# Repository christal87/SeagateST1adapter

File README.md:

# SeagateST1adapter

This is a quick and dirty 40 or 44 pin IDE adapter for Seagate ST1 drives with ATA Flex interface.  
These drives were common in mid- to high-end portable music players between 2000-2008.  

My PCB was quickly routed with FreeRouting using an exported Specctra session file from KiCAD.  
I have tested raw and unpartitioned writes with dd, filling an ST650211FX disk with about 1GB of zeroes shown 3MB/s throughtput at an average.  
  
Check out the wikipedia article about these disks [here](https://en.wikipedia.org/wiki/Seagate_ST1).  
Also Hans-Jürgen Reggel experimented with them awhile ago. Which you can see [here](http://www.hjreggel.net/hdtechdat/hd-seagate.html).  
  
##### Known ST1 HDDs with ATA Flex interface:
  
- ST625211FX (2.5GB) (2004)
- ST650211FX (5GB) (2004)
- ST64022FX (4GB) (2005)
- ST66022FX (6GB) (2005)
- ST68022FX (8GB) (2005)

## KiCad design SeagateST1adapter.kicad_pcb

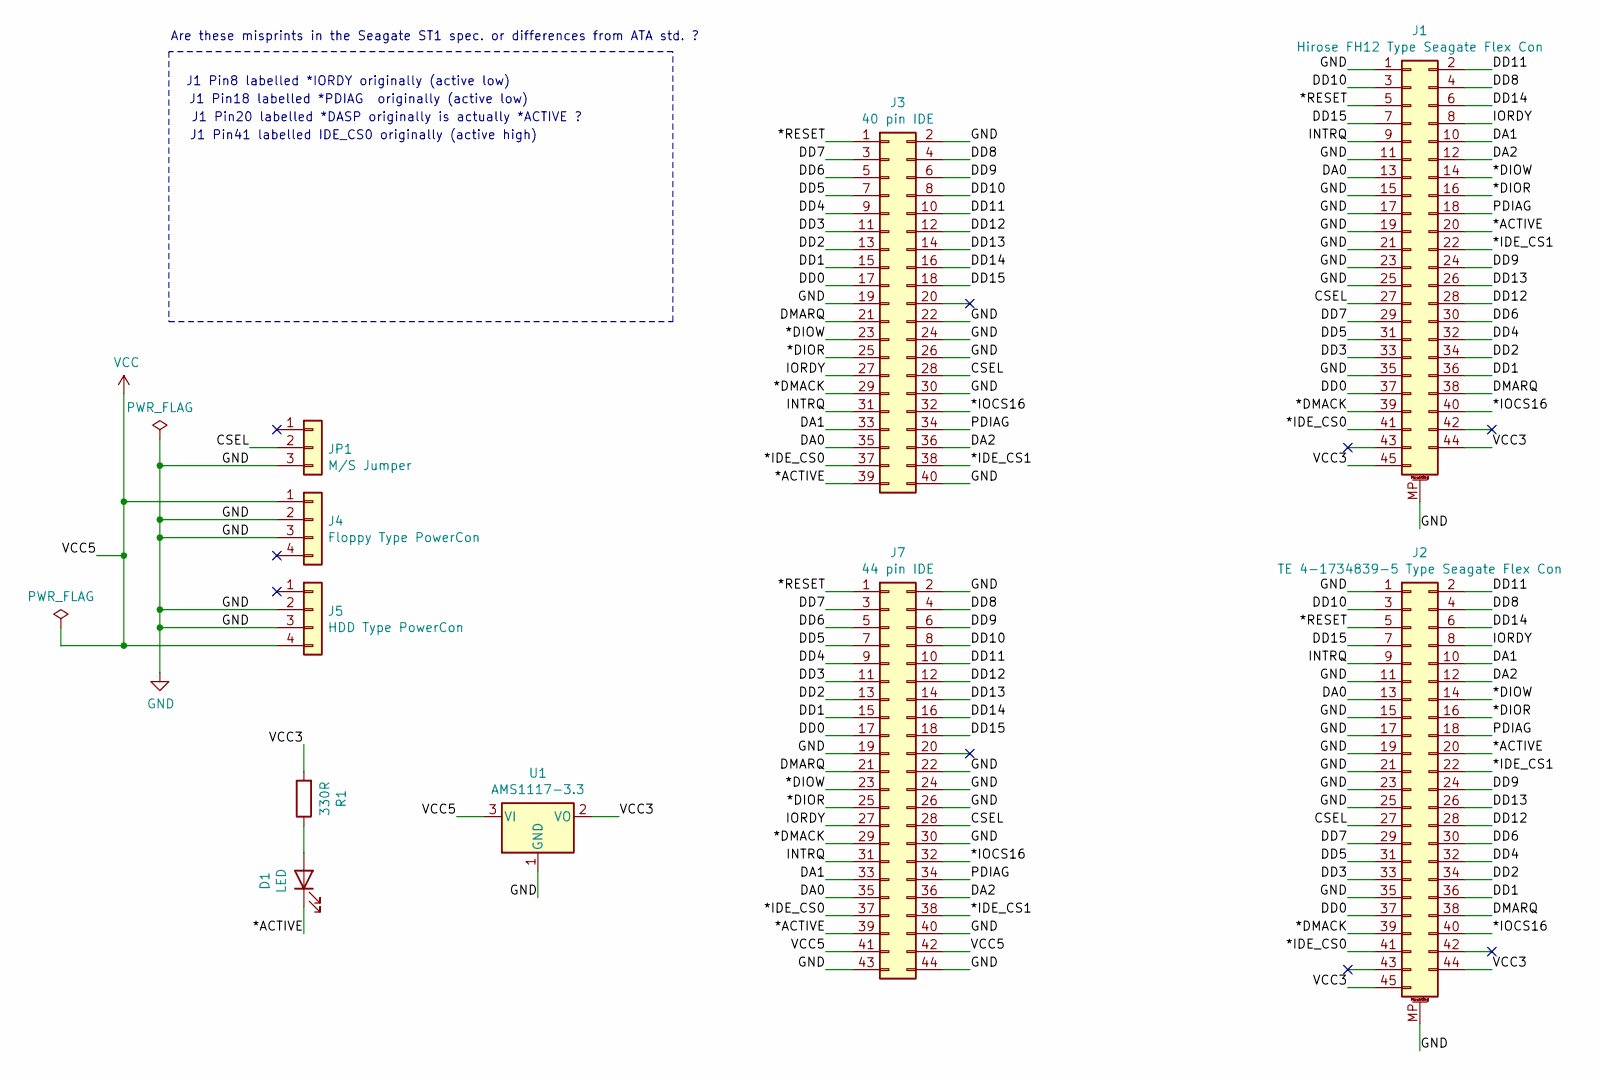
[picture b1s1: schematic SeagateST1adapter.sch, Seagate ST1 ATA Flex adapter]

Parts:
D1: LED; LED_D3.0mm
J1: Hirose FH12 Type Seagate Flex Con; Hirose_FH12-45S-0.5SH_1x45-1MP_P0.50mm_Horizontal
J2: TE 4-1734839-5 Type Seagate Flex Con; TE_4-1734839-5_1x45-1MP_P0.5mm_Horizontal
J3: 40 pin IDE; IDC-Header_2x20_P2.54mm_Vertical
J4: Floppy Type PowerCon; Molex_KK-254_AE-6410-04A_1x04_P2.54mm_Vertical
J5: HDD Type PowerCon; TE_MATE-N-LOK_350211-1_1x04_P5.08mm_Vertical
J7: 44 pin IDE; PinHeader_2x22_P2.00mm_Vertical
JP1: M/S Jumper; PinHeader_1x03_P2.54mm_Vertical
R1: 330R; R_Axial_DIN0207_L6.3mm_D2.5mm_P7.62mm_Horizontal
U1: AMS1117-3.3; SOT-223-3_TabPin2

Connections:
/*ACTIVE: D1.1 (K), J1.20, J2.20, J3.39, J7.39
/*DIOR: J1.16, J2.16, J3.25, J7.25
/*DIOW: J1.14, J2.14, J3.23, J7.23
/*DMACK: J1.39, J2.39, J3.29, J7.29
/*IDE_CS0: J1.41, J2.41, J3.37, J7.37
/*IDE_CS1: J1.22, J2.22, J3.38, J7.38
/*IOCS16: J1.40, J2.40, J3.32, J7.32
/*RESET: J1.5, J2.5, J3.1, J7.1
/CSEL: J1.27, J2.27, J3.28, J7.28, JP1.2
/DA0: J1.13, J2.13, J3.35, J7.35
/DA1: J1.10, J2.10, J3.33, J7.33
/DA2: J1.12, J2.12, J3.36, J7.36
/DD0: J1.37, J2.37, J3.17, J7.17
/DD1: J1.36, J2.36, J3.15, J7.15
/DD2: J1.34, J2.34, J3.13, J7.13
/DD3: J1.33, J2.33, J3.11, J7.11
/DD4: J1.32, J2.32, J3.9, J7.9
/DD5: J1.31, J2.31, J3.7, J7.7
/DD6: J1.30, J2.30, J3.5, J7.5
/DD7: J1.29, J2.29, J3.3, J7.3
/DD8: J1.4, J2.4, J3.4, J7.4
/DD9: J1.24, J2.24, J3.6, J7.6
/DD10: J1.3, J2.3, J3.8, J7.8
/DD11: J1.2, J2.2, J3.10, J7.10
/DD12: J1.28, J2.28, J3.12, J7.12
/DD13: J1.26, J2.26, J3.14, J7.14
/DD14: J1.6, J2.6, J3.16, J7.16
/DD15: J1.7, J2.7, J3.18, J7.18
/DMARQ: J1.38, J2.38, J3.21, J7.21
/INTRQ: J1.9, J2.9, J3.31, J7.31
/IORDY: J1.8, J2.8, J3.27, J7.27
/PDIAG: J1.18, J2.18, J3.34, J7.34
/VCC3: J1.44, J1.45, J2.44, J2.45, R1.2, U1.2 (VO)
GND: J1.1, J1.11, J1.15, J1.17, J1.19, J1.21, J1.23, J1.25, J1.35, J1.MP (MountPin), J2.1, J2.11, J2.15, J2.17, J2.19, J2.21, J2.23, J2.25, J2.35, J2.MP (MountPin), J3.2, J3.19, J3.22, J3.24, J3.26, J3.30, J3.40, J4.2, J4.3, J5.2, J5.3, J7.2, J7.19, J7.22, J7.24, J7.26, J7.30, J7.40, J7.43, J7.44, JP1.3, U1.1 (GND)
unnamed: D1.2 (A), R1.1
VCC: J4.1, J5.4, J7.41, J7.42, U1.3 (VI)

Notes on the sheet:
J1 Pin8 labelled *IORDY originally (active low)
J1 Pin18 labelled *PDIAG originally (active low)
J1 Pin20 labelled *DASP originally is actually *ACTIVE ?
J1 Pin41 labelled IDE_CS0 originally (active high)
Are these misprints in the Seagate ST1 spec. or differences from ATA std. ?

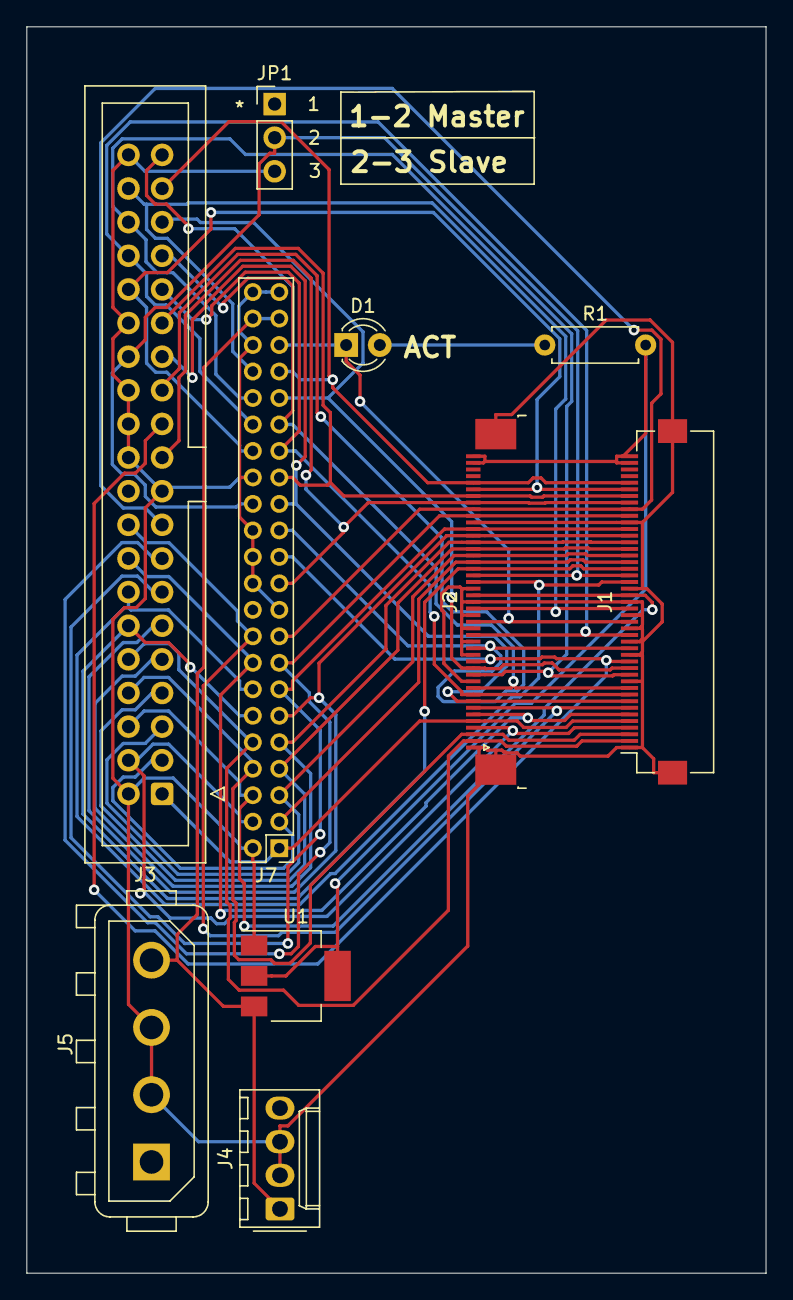
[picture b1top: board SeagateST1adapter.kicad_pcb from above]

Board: 2 copper layers, 55.8 x 94.1 mm, 10 parts (0 on the bottom side), 36 nets.

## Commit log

2020-11-27 Revision 1 (tested)
2020-11-27 Update README.md
    Revision 1 docs update
2020-11-27 Add images
2020-11-27 Update README.md
    Add illustration
